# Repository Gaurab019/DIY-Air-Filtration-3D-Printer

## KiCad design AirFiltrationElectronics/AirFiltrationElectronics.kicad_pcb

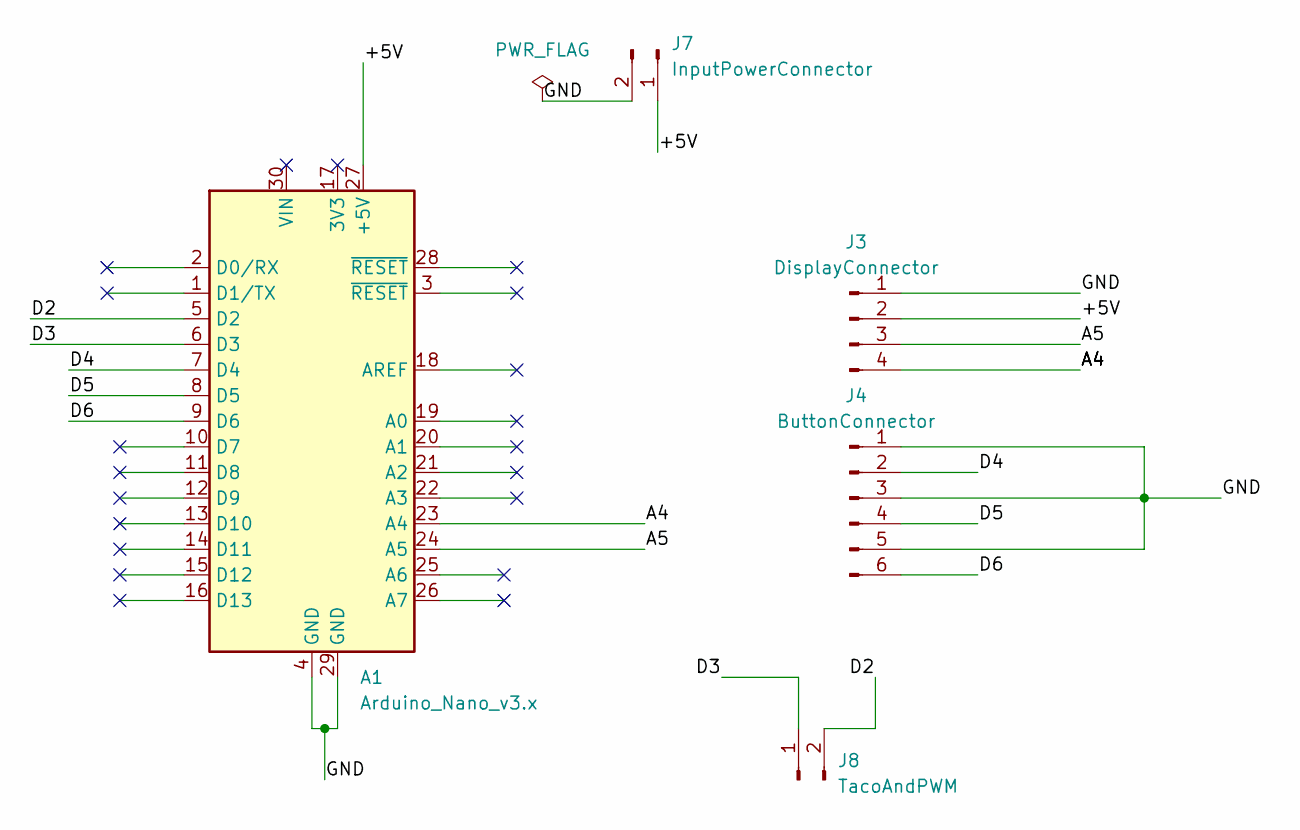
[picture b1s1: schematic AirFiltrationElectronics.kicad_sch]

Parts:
A1: Arduino_Nano_v3.x; Arduino_Nano
J3: DisplayConnector; PinHeader_1x04_P2.54mm_Vertical
J4: ButtonConnector; PinHeader_1x06_P2.54mm_Vertical
J7: InputPowerConnector; PinHeader_1x02_P2.54mm_Vertical
J8: TacoAndPWM; PinHeader_1x02_P2.54mm_Vertical

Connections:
/+5V: A1.27 (+5V), J3.2, J7.1
/A4: A1.23 (A4), J3.4
/A5: A1.24 (A5), J3.3
/D2: A1.5 (D2), J8.2
/D3: A1.6 (D3), J8.1
/D4: A1.7 (D4), J4.2
/D5: A1.8 (D5), J4.4
/D6: A1.9 (D6), J4.6
/GND: A1.4 (GND), A1.29 (GND), J3.1, J4.1, J4.3, J4.5, J7.2

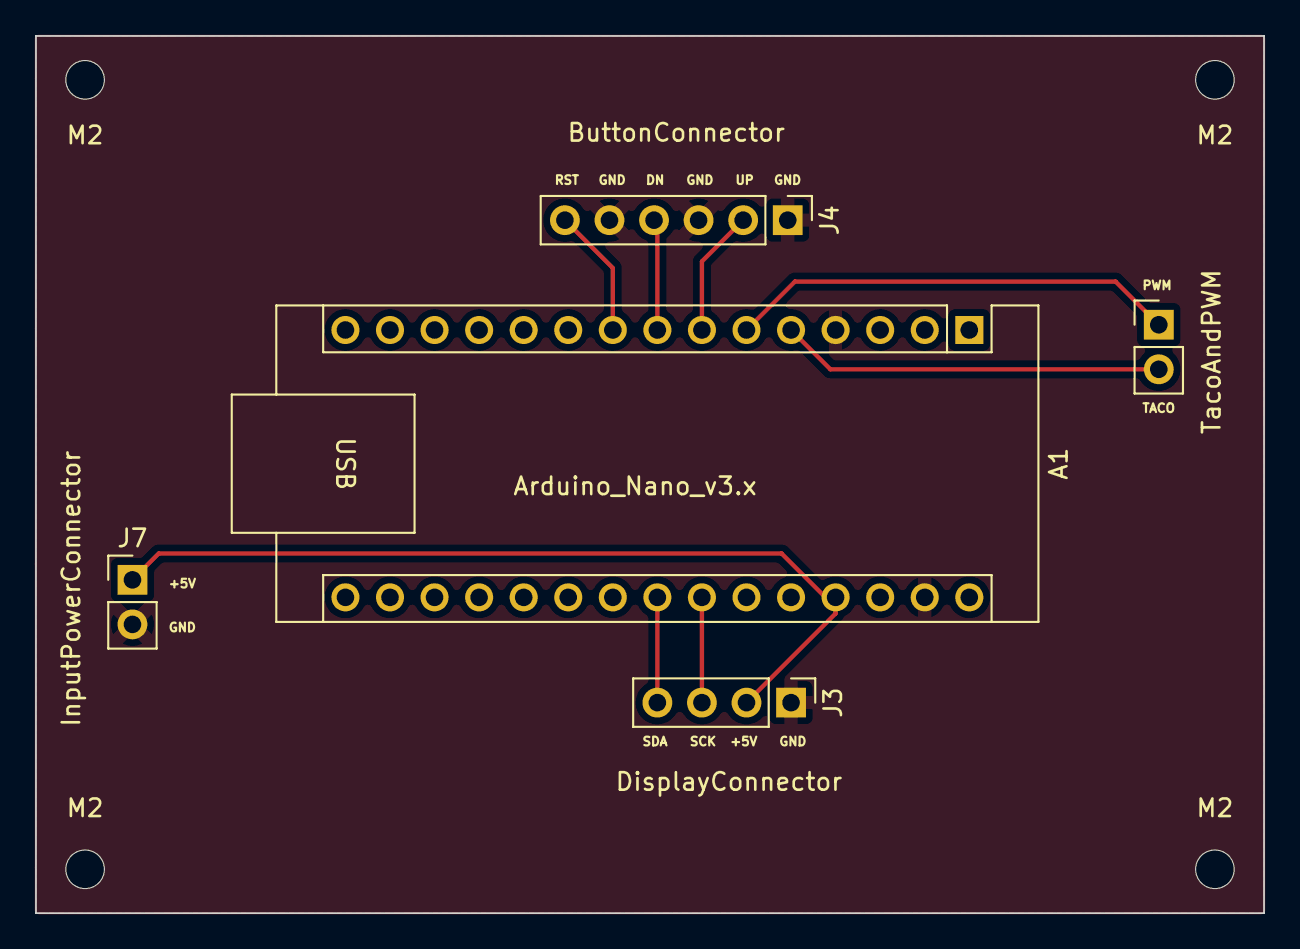
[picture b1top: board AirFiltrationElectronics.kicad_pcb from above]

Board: 2 copper layers, 70.0 x 50.0 mm, 5 parts (0 on the bottom side), 9 nets.

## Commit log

2026-05-16 All Available files for the filtration
2026-05-16 Kicad Files
